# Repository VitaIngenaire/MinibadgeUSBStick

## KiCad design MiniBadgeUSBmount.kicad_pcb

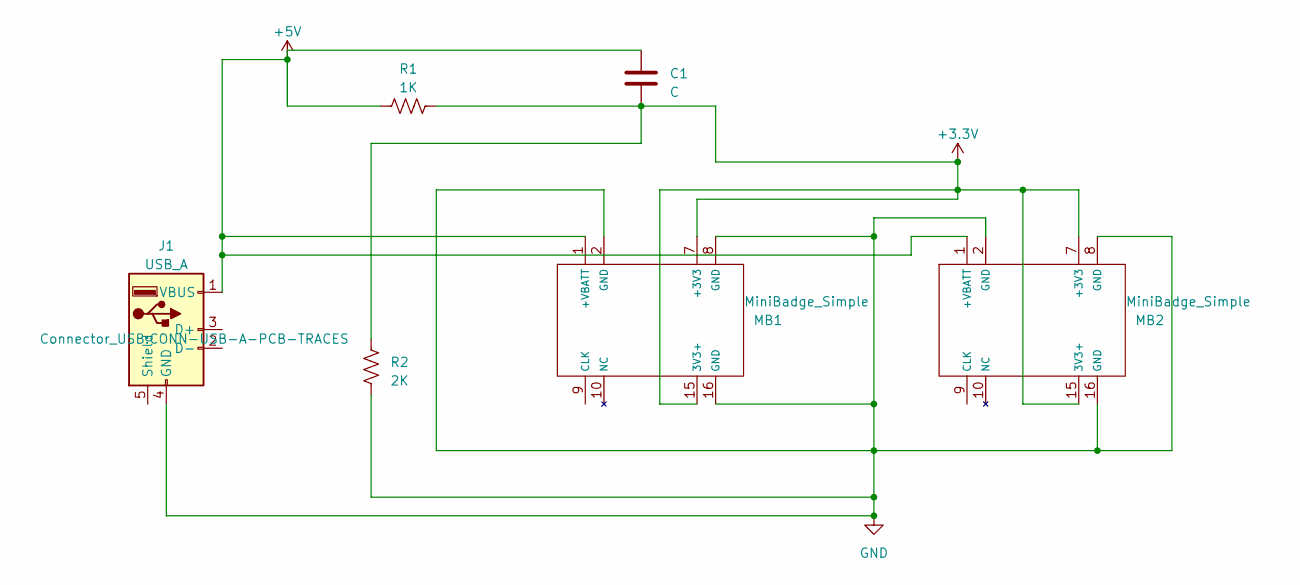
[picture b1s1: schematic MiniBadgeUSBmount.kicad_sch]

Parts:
C1: C; C_Disc_D7.5mm_W5.0mm_P5.00mm
J1: USB_A; CONN-USB-A-PCB-TRACES
MB1, MB2: MiniBadge_Simple; MiniBadge_Simple_NoEdges
R1: 1K; R_Axial_DIN0207_L6.3mm_D2.5mm_P10.16mm_Horizontal
R2: 2K; R_Axial_DIN0207_L6.3mm_D2.5mm_P10.16mm_Horizontal

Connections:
+3.3V: C1.2, MB1.7 (+3V3), MB1.15 (3V3+), MB2.7 (+3V3), MB2.15 (3V3+), R1.2, R2.2
+5V: C1.1, J1.1 (VBUS), MB1.1 (+VBATT), MB2.1 (+VBATT), R1.1
GND: J1.4 (GND), MB1.2 (GND), MB1.8 (GND), MB1.16 (GND), MB2.2 (GND), MB2.8 (GND), MB2.16 (GND), R2.1

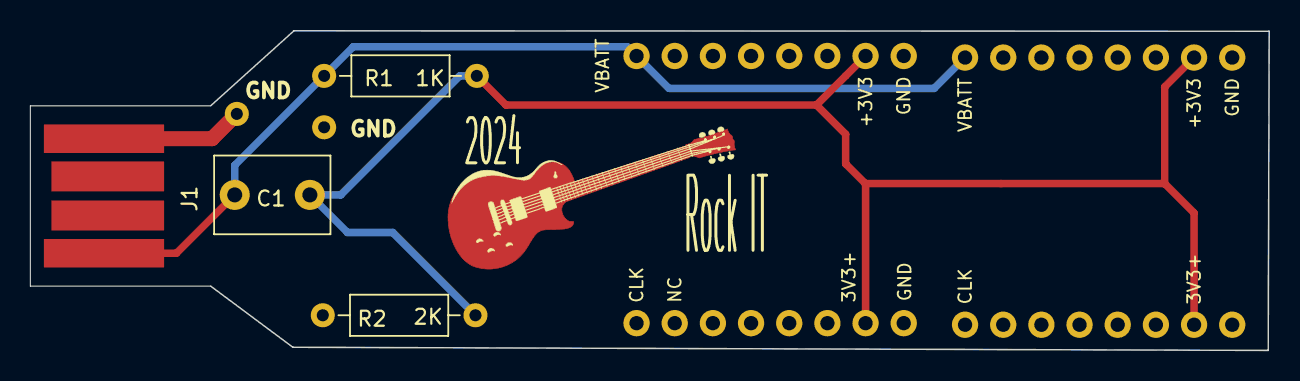
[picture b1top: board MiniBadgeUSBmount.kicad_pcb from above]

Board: 2 copper layers, 82.4 x 21.3 mm, 6 parts (0 on the bottom side), 3 nets.

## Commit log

2023-12-29 Add files via upload
    Initial commit for prototype pcb production.
